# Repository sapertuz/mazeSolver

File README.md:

<h1 align="center">Open-Source mazeSolver</h1>
<div align="center">

<i>A Maze Solving Line Follower Using Arduino</i>

<!--  -->

<br>
<i>Loved the project? Please consider giving a Star ⭐️ to help it improve!</i>

</div>

# mazeSolver

This Git contains the 
- Arduino Project Source  https://github.com/cheiio/mazeSolver/tree/master/Arduino_src
- Eagle Source for PCB board  https://github.com/cheiio/mazeSolver/tree/master/Laberinto
- SolidWorks files of parts to be printed  https://github.com/cheiio/mazeSolver/tree/master/Maze_Solver/files

This is the arduino program running ont he maze solver project viewed in http://www.thingiverse.com/thing:1690543
You need the PID_v1 library fot arduino to make irt run

This is a current working project. It's a 3D printed Maze Solver and Line Follower based on the Pololu 3Pi robot.
It uses a Arduino Leonardo and a custom made shield.
<br />

## Materials

***<details><summary>Click Me For Materials!</summary>***
  
* Arduino Leonardo
* L293D
* Piezo Buzzer
* QTR-1RC Reflectance Sensor (2-Pack) x 2 (https://www.pololu.com/product/2459)
* QTR-8A Reflectance Sensor Array (Only the cutted 2 sensor at the left) https://www.pololu.com/product/960
* 75:1 Micro Metal Gearmotor HPCB 6V (https://www.pololu.com/product/3064)
* Pololu Wheel 42×19mm Pair (https://www.pololu.com/product/1090)
* Pololu Micro Metal Gearmotor Bracket Pair
* (https://www.pololu.com/product/989)
* Pololu Ball Caster with 1/2″ Metal Ball (https://www.pololu.com/product/953)
* 2-AA Batteries
* 2-AA Battery Holder (https://www.pololu.com/product/1150)
</details>
<br />

### Robot In Action

<br />

## CAD Files

</a>

</a>

</a>

<br /><br />

## Line Follower Photos

<br />

## YouTube Video
</a>

For Robot in action Please checkout my<br />
**Youtube Channel  [Click Here](https://www.youtube.com/watch?v=Ddkci5myxYI&feature=youtu.be)** .<br /><br /><br />

If You Found this Project Useful in any manner <br />
**Subscribe** my **Youtube Channel  [Click Here](https://www.youtube.com/user/Sapmcool)** .<br />

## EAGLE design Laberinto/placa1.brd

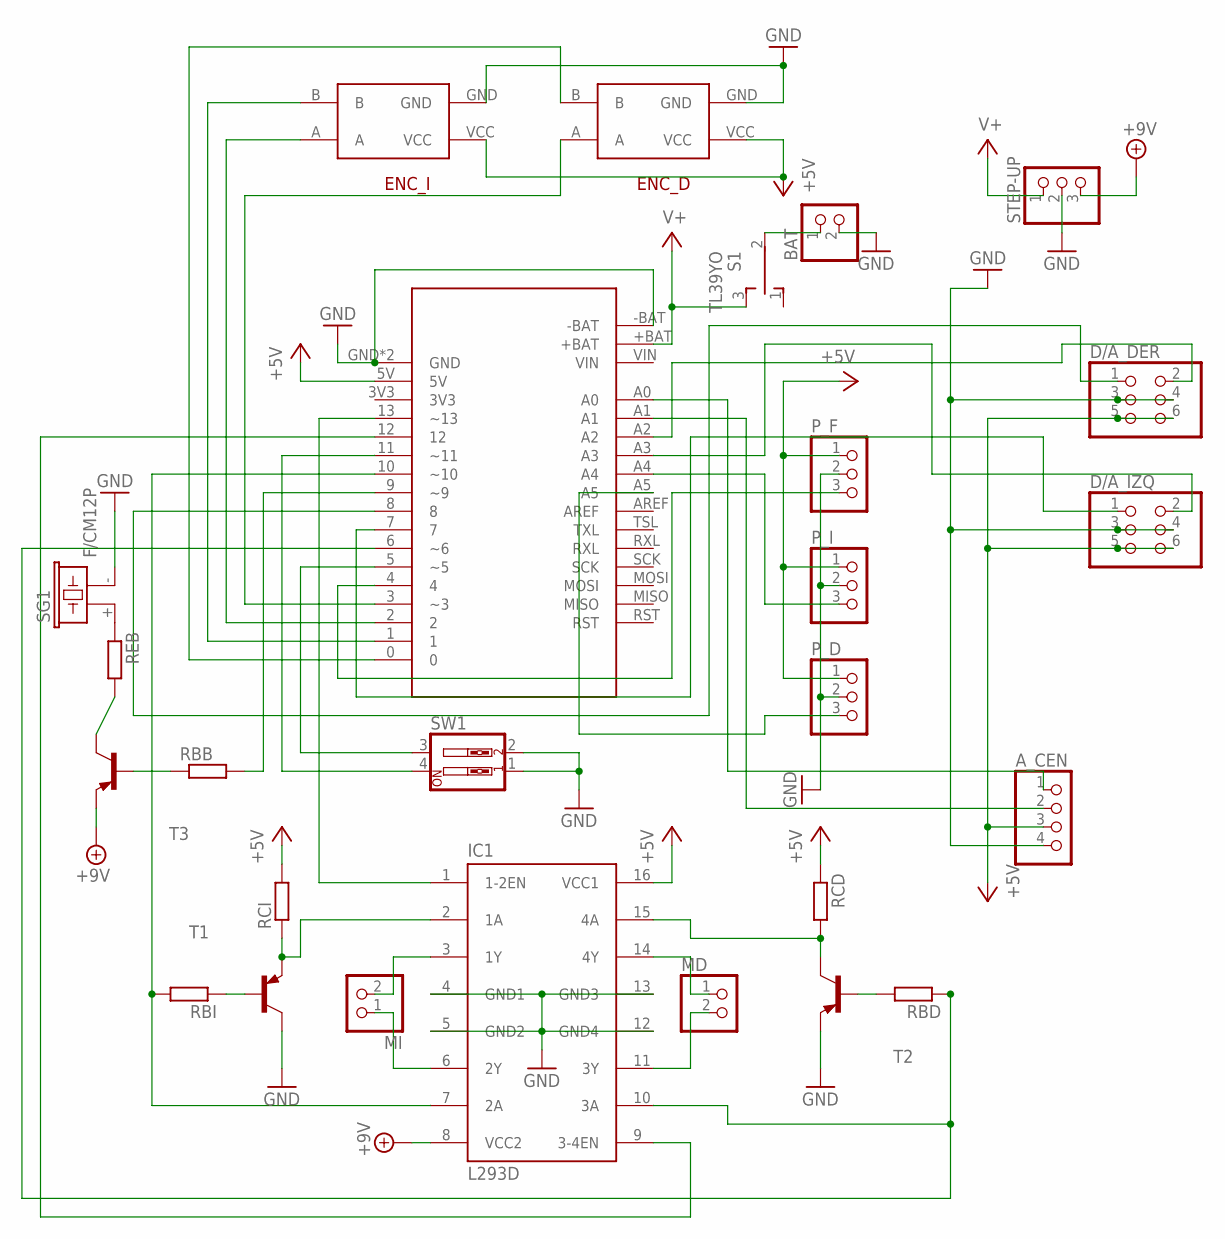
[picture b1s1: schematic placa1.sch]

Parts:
A_CEN: PINHD-1X4/90; 1X04/90
BAT: PINHD-1X2; 1X02
D/A_DER: PINHD-2X3/90; 2X03/90
D/A_IZQ: PINHD-2X3/90; 2X03/90
ENC_D: POLOLU_ENCODER
ENC_I: POLOLU_ENCODER
IC1: L293D; DIL16
MD: PINHD-1X2; 1X02
MI: PINHD-1X2; 1X02
P_D: PINHD-1X3/90; 1X03/90
P_F: PINHD-1X3; 1X03
P_I: PINHD-1X3/90; 1X03/90
RBB: R0204/7; 0204/7
RBD: R0204/7; 0204/7
RBI: R0204/7; 0204/7
RCD: R0204/7; 0204/7
RCI: R0204/7; 0204/7
REB: R0204/7; 0204/7
S1: TL39YO; TL3XYO
SG1: F/CM12P
STEP-UP: PINHD-1X3; 1X03
SW1: SW_DIP-2; EDG-02
T1, T2, T3: -PNP-TO92-BEC; TO92-BEC
U$1: A-STAR_LV

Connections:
+5V: A_CEN.3, D/A_DER.5, D/A_DER.6, D/A_IZQ.5, D/A_IZQ.6, ENC_D.VCC, ENC_I.VCC, IC1.16 (VCC1), P_D.1, P_F.1, P_I.1, RCD.1, RCI.2, U$1.5V
+9V: IC1.8 (VCC2), STEP-UP.3, T3.E
GND: A_CEN.4, BAT.2, D/A_DER.3, D/A_DER.4, D/A_IZQ.3, D/A_IZQ.4, ENC_D.GND, ENC_I.GND, IC1.4 (GND1), IC1.5 (GND2), IC1.12 (GND4), IC1.13 (GND3), P_D.2, P_F.2, P_I.2, SG1.- (2), STEP-UP.2, SW1.1, SW1.2, T1.C, T2.E, U$1.-BAT, U$1.GND, U$1.GND2 (GND)
unnamed: BAT.1, S1.2
unnamed: IC1.2 (1A), RCI.1, T1.E
unnamed: RBI.1, T1.B
unnamed: RBD.2, T2.B
unnamed: IC1.15 (4A), RCD.2, T2.C
unnamed: IC1.11 (3Y), MD.2
unnamed: IC1.14 (4Y), MD.1
unnamed: IC1.7 (2A), RBI.2, U$1.10 (~10)
unnamed: IC1.3 (1Y), MI.2
unnamed: IC1.6 (2Y), MI.1
unnamed: IC1.10 (3A), RBD.1, U$1.6 (~6)
unnamed: REB.2, T3.C
unnamed: REB.1, SG1.+ (1)
unnamed: RBB.1, T3.B
unnamed: ENC_I.A, U$1.2
unnamed: ENC_D.B, U$1.0
unnamed: ENC_I.B, U$1.1
unnamed: IC1.9 (3-4EN), U$1.12
unnamed: SW1.3, U$1.5 (~5)
unnamed: SW1.4, U$1.11 (~11)
unnamed: RBB.2, U$1.9 (~9)
unnamed: ENC_D.A, U$1.3 (~3)
unnamed: IC1.1 (1-2EN), U$1.13 (~13)
unnamed: P_F.3, U$1.4
unnamed: D/A_IZQ.1, U$1.7
unnamed: D/A_DER.1, U$1.8
unnamed: A_CEN.1, U$1.A0
unnamed: D/A_IZQ.2, U$1.A3
unnamed: P_I.3, U$1.A4
unnamed: P_D.3, U$1.A5
unnamed: A_CEN.2, U$1.A1
unnamed: D/A_DER.2, U$1.A2
V+: S1.3 (S), STEP-UP.1, U$1.+BAT

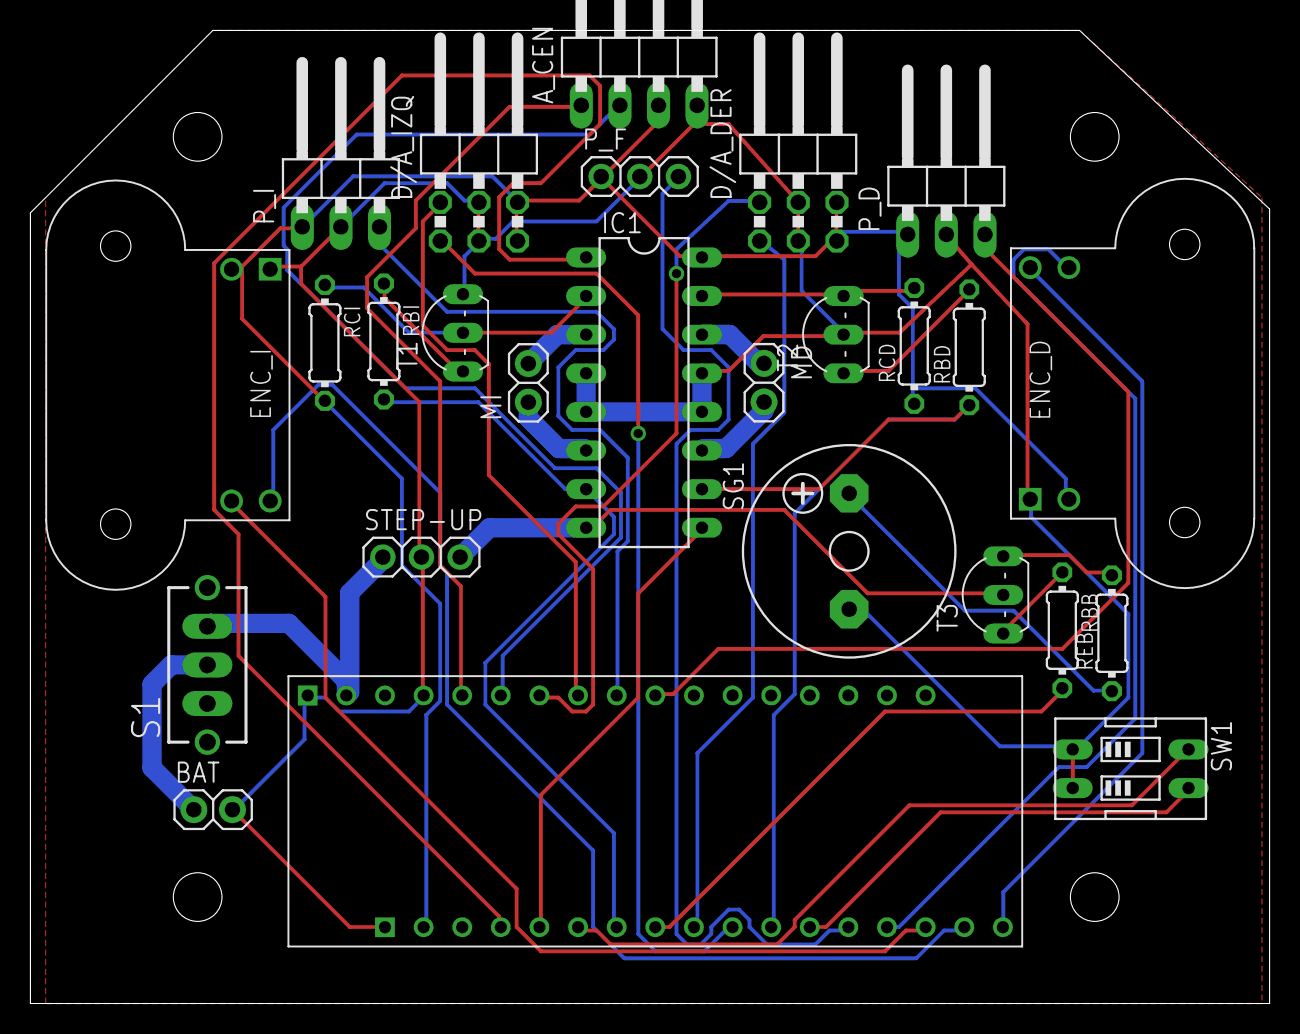
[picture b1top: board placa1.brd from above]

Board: 2 copper layers, 81.5 x 64.0 mm, 26 parts (0 on the bottom side), 36 nets.

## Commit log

2016-10-22 Maze Solver Robot
    Arduino project for the maze solver robot made by Sergio Pertuz; It
    needs the PID_v1.h library for arduino
2020-05-10 new files, complete project
